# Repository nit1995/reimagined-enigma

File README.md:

# reimagined-enigma
India-H20 Project

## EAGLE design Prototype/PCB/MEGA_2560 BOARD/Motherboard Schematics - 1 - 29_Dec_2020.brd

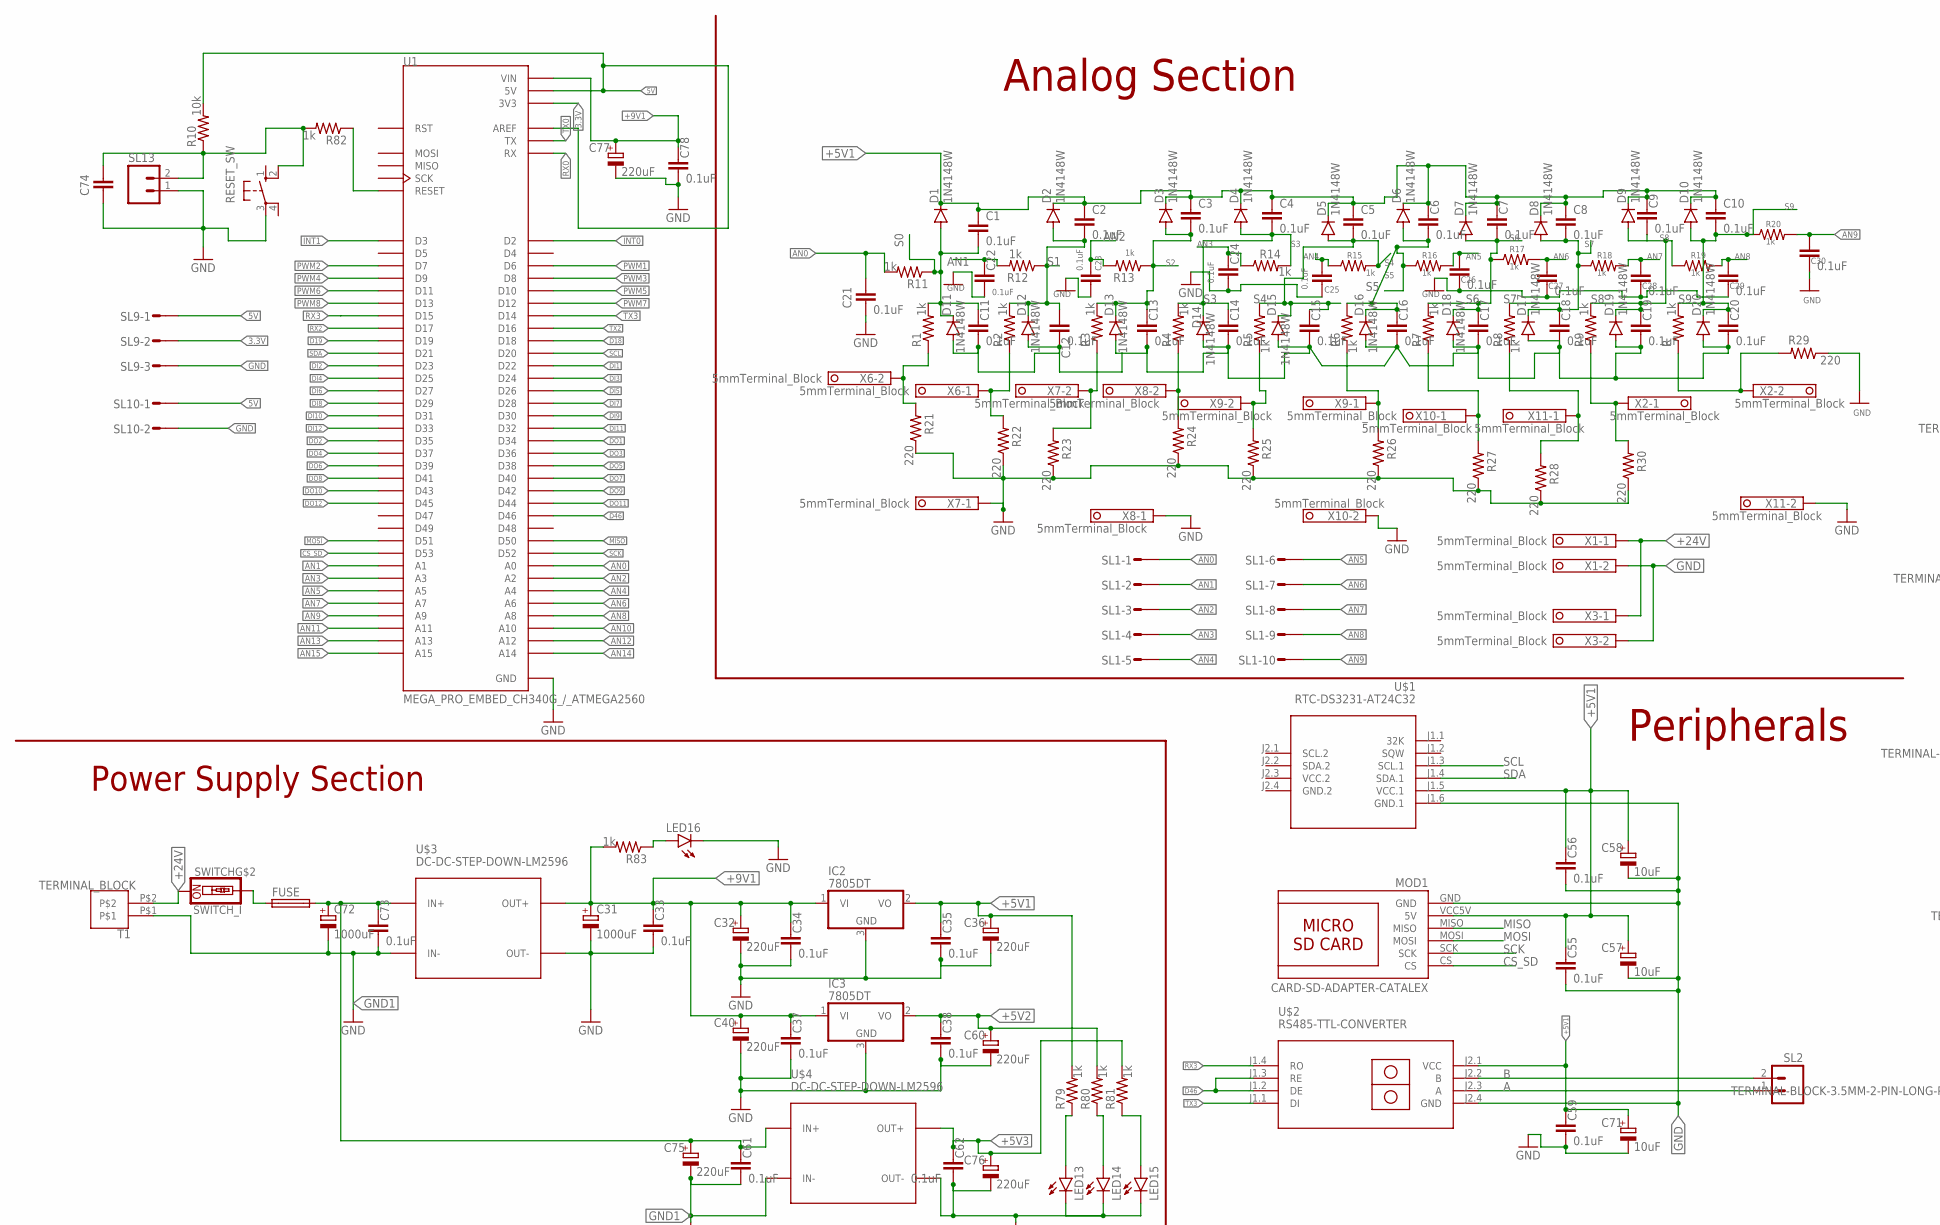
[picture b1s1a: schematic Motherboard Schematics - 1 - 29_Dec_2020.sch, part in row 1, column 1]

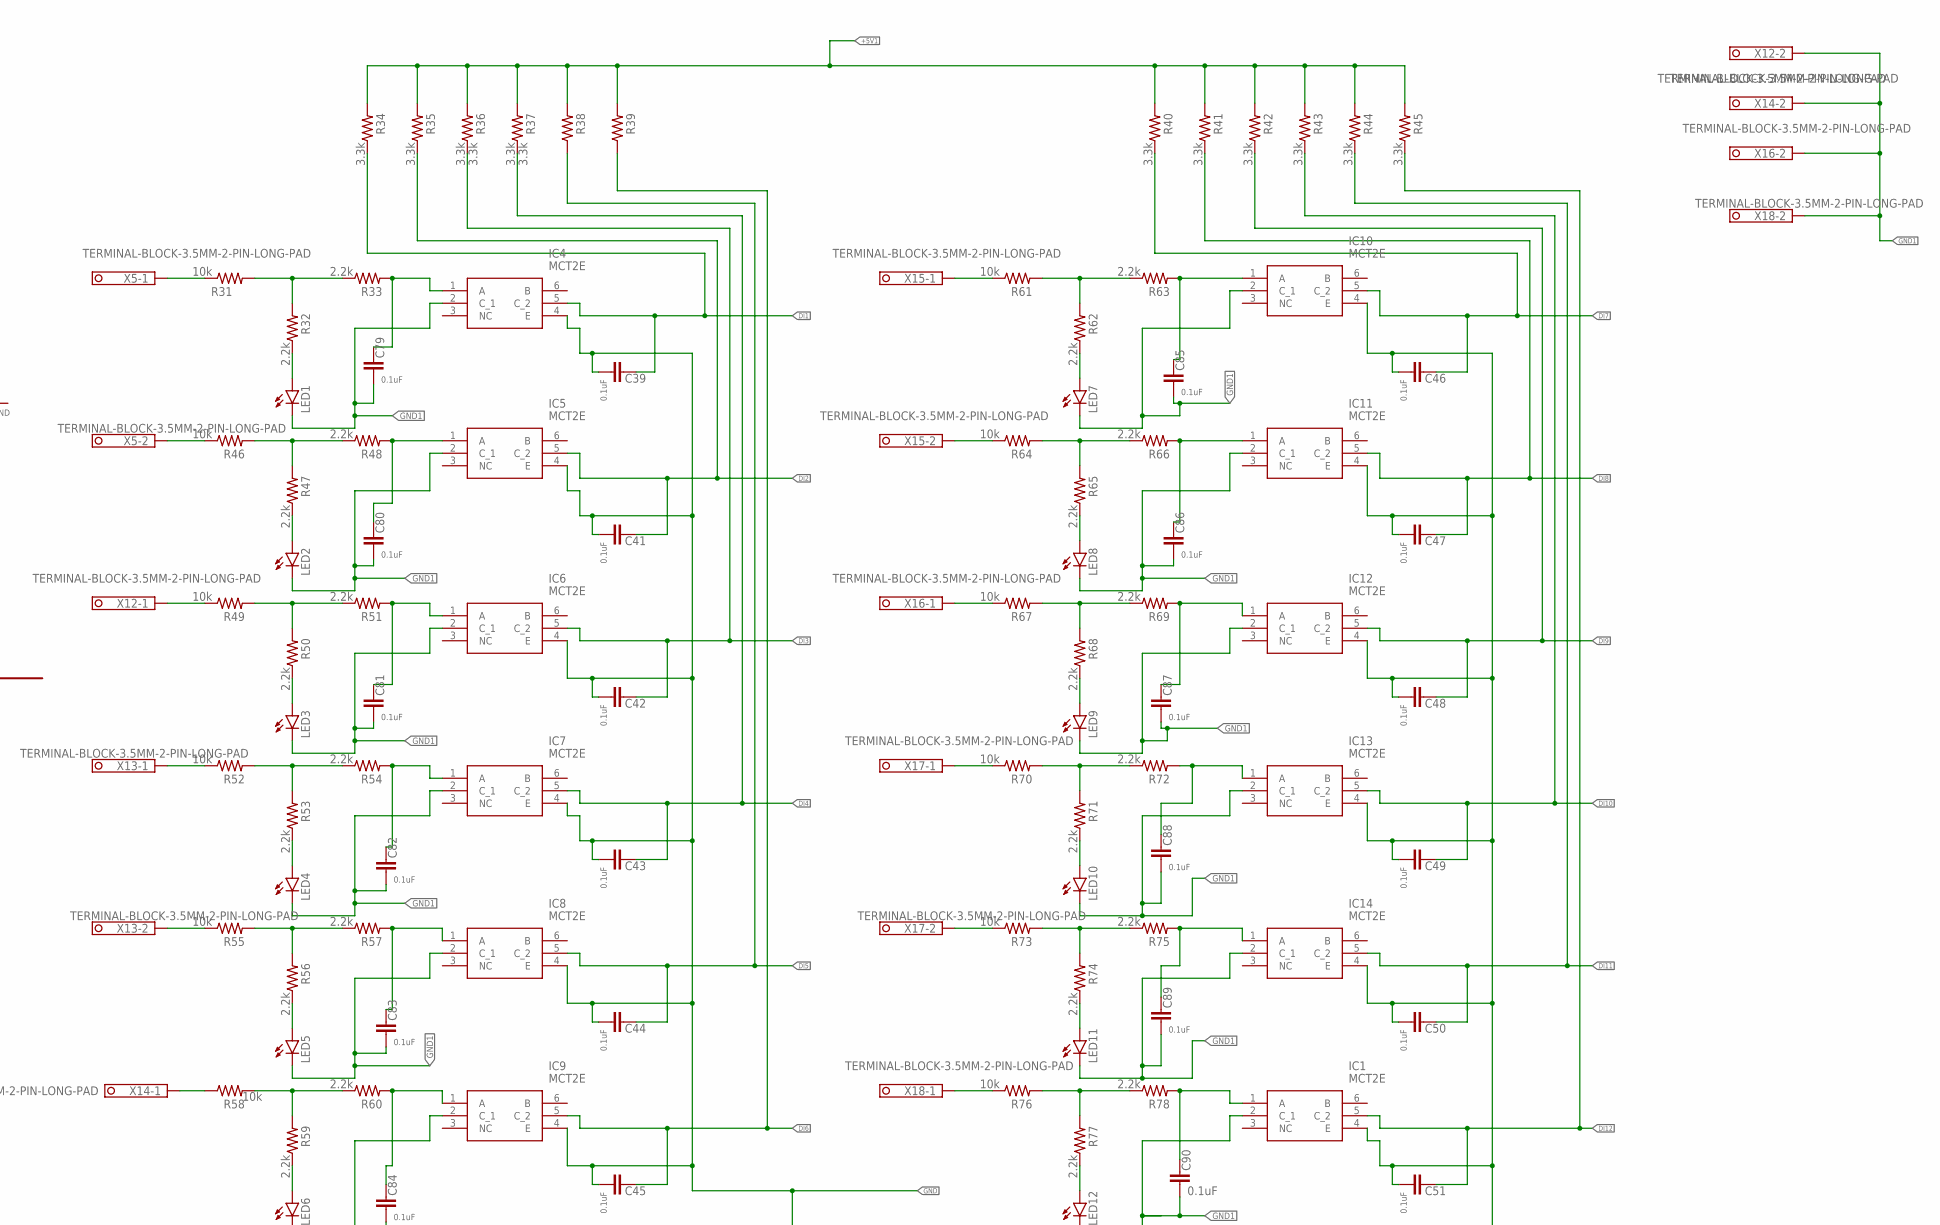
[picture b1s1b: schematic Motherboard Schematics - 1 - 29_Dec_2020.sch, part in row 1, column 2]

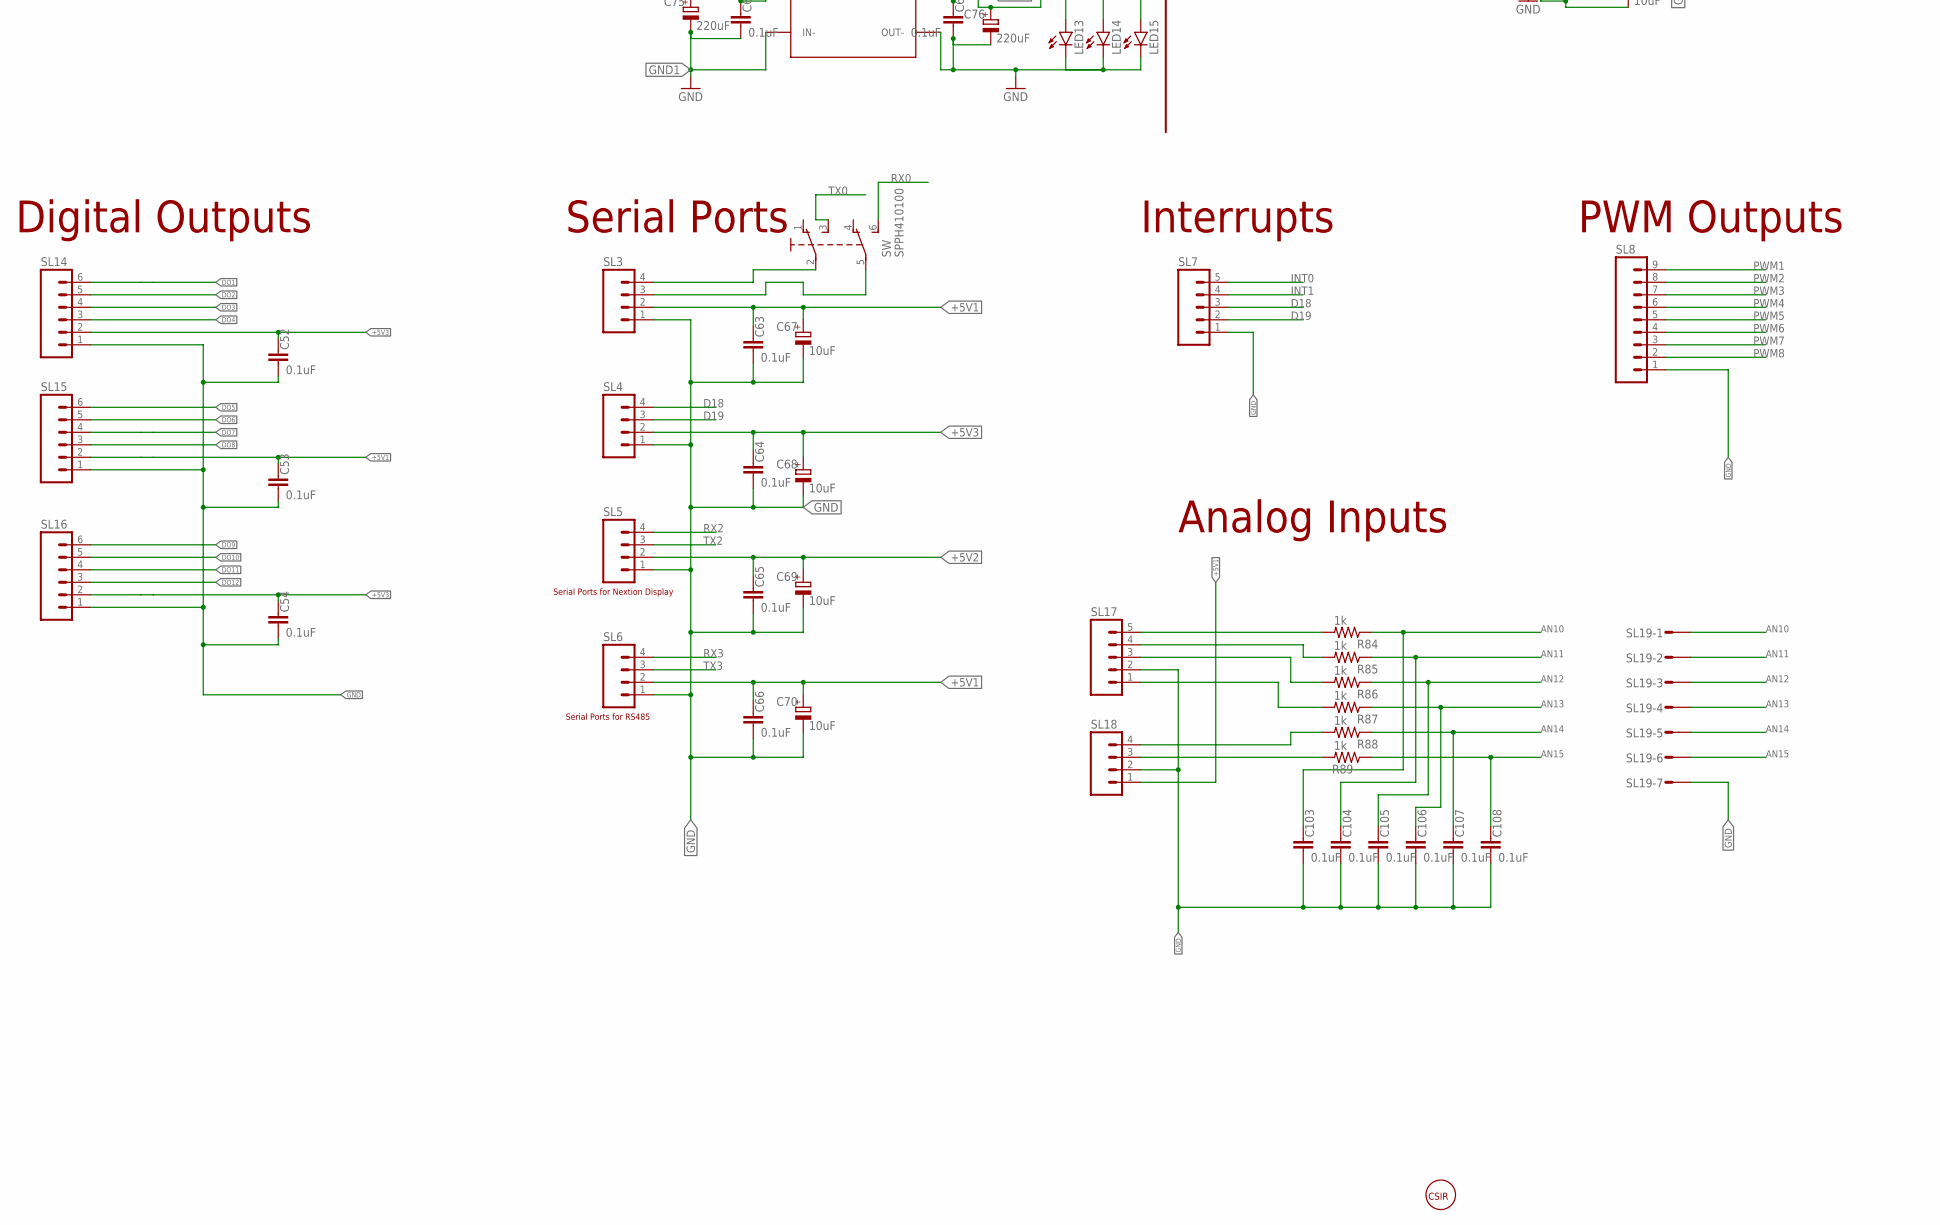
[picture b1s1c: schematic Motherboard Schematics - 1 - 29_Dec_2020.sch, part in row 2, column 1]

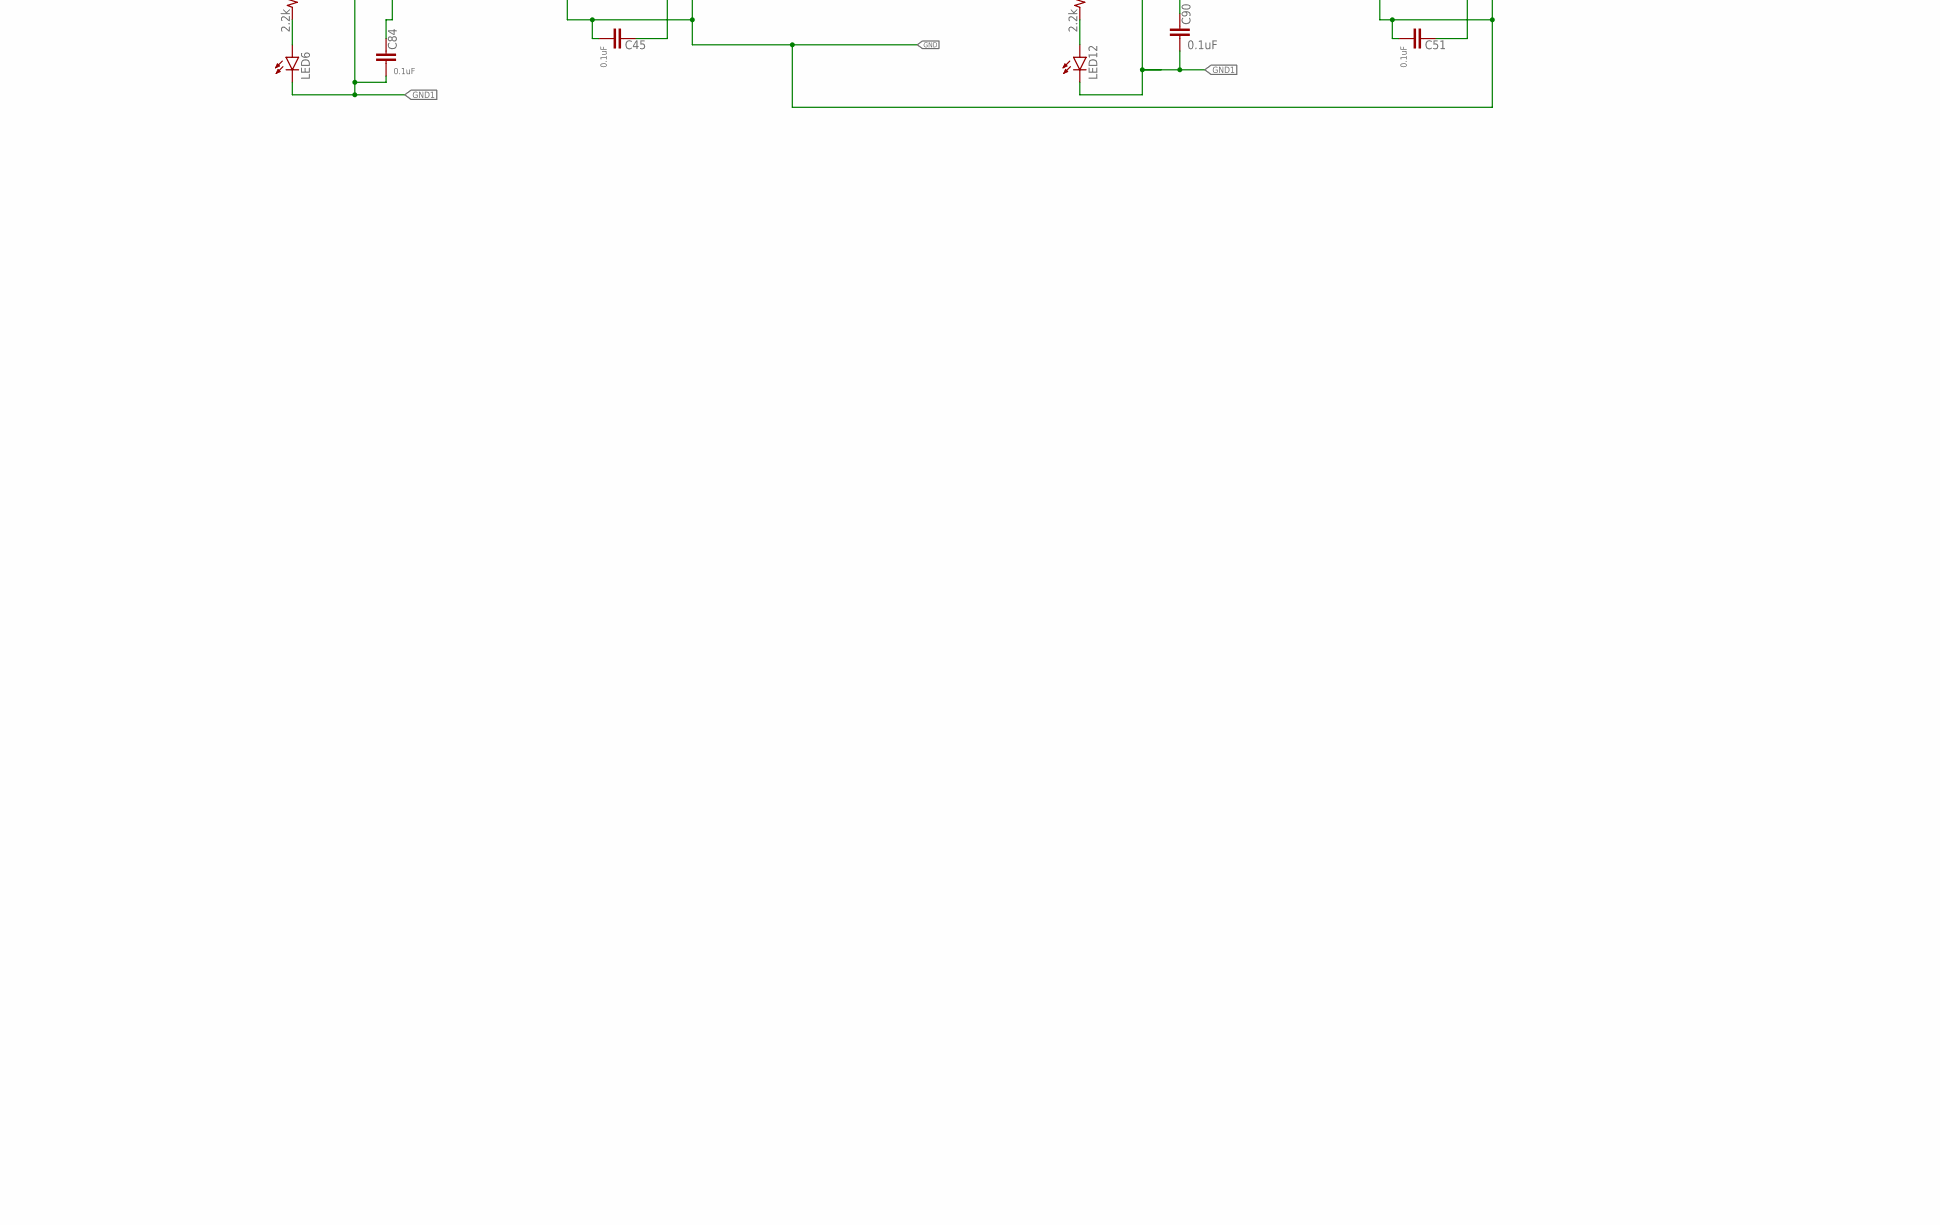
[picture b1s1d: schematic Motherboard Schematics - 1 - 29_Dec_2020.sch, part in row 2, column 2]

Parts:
C1, C2, C3, C4, C5, C6, C7, C8, C9, C10, C11, C12, C13, C14, C15, C16, C17, C18, C19, C20, C21, C22, C23, C24, C25, C26, C27, C28, C29, C30, C33, C34, C35, C37, C38, C39, C41, C42, C43, C44, C45, C46, C47, C48, C49, C50, C51, C52, C53, C54, C55, C56, C59, C61, C62, C63, C64, C65, C66, C73, C74, C78, C79, C80, C81, C82, C83, C84, C85, C86, C87, C88, C89, C90, C103, C104, C105, C106, C107, C108: 0.1uF; C1206
C31, C72: 1000uF; E7,5-16
C32, C36, C40, C60, C75, C76, C77: 220uF; E5-10,5
C57, C58, C67, C68, C69, C70, C71: 10uF; E2,5-7
D1, D2, D3, D4, D5, D6, D7, D8, D9, D10, D11, D12, D13, D14., D15, D16, D17, D18, D19, D20: 1N4148W; DO214AC
FUSE: SH22,5A
IC1, IC4, IC5, IC6, IC7, IC8, IC9, IC10, IC11, IC12, IC13, IC14: MCT2E; DIP762W60P254L712H480Q6N
IC2, IC3: 7805DT; TO252
LED1, LED2, LED3, LED4, LED5, LED6, LED7, LED8, LED9, LED10, LED11, LED12, LED13, LED14, LED15, LED16: LEDCHIPLED_1206; CHIPLED_1206
MOD1: CARD-SD-ADAPTER-CATALEX
R, R1, R2, R3, R4, R5, R6, R7, R8, R9, R11, R12, R13, R14, R15, R16, R17, R18, R19, R20, R79, R80, R81, R82, R83, R84, R85, R86, R87, R88, R89: 1k; R1206
R10, R31, R46, R49, R52, R55, R58, R61, R64, R67, R70, R73, R76: 10k; R1206
R21, R22, R23, R24, R25, R26, R27, R28, R29, R30: 220; R1206
R32, R33, R47, R48, R50, R51, R53, R54, R56, R57, R59, R60, R62, R63, R65, R66, R68, R69, R71, R72, R74, R75, R77, R78: 2.2k; R1206
R34, R35, R36, R37, R38, R39, R40, R41, R42, R43, R44, R45: 3.3k; R1206
RESET_SW: 10-XX; B3F-10XX
SL1: M10S; 10P
SL2, SL13: M02; 02P
SL3, SL4, SL5, SL6, SL18: M04; 04P
SL7, SL17: M05; 05P
SL8: M09; 09P
SL9: M03S; 03P
SL10: M02S; 02P
SL14, SL15, SL16: M06; 06P
SL19: M07S; 07P
SW: SPPH410100
SWITCH: SWITCH_I
T1: TERMINAL_BLOCK; BOC_TERMINAL
U1: MEGA_PRO_EMBED_CH340G_/_ATMEGA2560; MODULE_MEGA_PRO_EMBED_CH340G_/_ATMEGA2560
U$1: RTC-DS3231-AT24C32
U$2: RS485-TTL-CONVERTER
U$3, U$4: DC-DC-STEP-DOWN-LM2596
U$5: CSIR_LOGO
X1, X2, X3, X6, X7, X8, X9, X10, X11: 5mmTerminal_Block; TERMINAL-BLOCK-2-PIN-3.5MM-LONG-PAD
X5, X12, X13, X14, X15, X16, X17, X18: TERMINAL-BLOCK-3.5MM-2-PIN-LONG-PAD; TERMINAL-BLOCK-2-PIN-3.5MM-LONG-PAD

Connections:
3.3V: SL9.2, U1.3V3_1 (3V3), U1.3V3_2 (3V3)
5V: R10.2, SL9.1, SL10.1, U1.5V_1 (5V), U1.5V_2 (5V), U1.5V_3 (5V), U1.AREF
+5V1: C1.1, C2.1, C3.1, C4.1, C5.1, C6.1, C7.1, C8.1, C9.1, C10.1, C35.1, C36.+, C53.1, C55.1, C56.1, C57.+, C58.+, C59.1, C63.1, C66.1, C67.+, C70.+, C71.+, D1.C, D2.C, D3.C, D4.C, D5.C, D6.C, D7.C, D8.C, D9.C, D10.C, IC2.2 (VO), MOD1.VCC5V (5V), R34.2, R35.2, R36.2, R37.2, R38.2, R39.2, R40.2, R41.2, R42.2, R43.2, R44.2, R45.2, R79.2, SL3.2, SL6.2, SL15.2, SL18.1, U$1.J1.5 (VCC.1), U$2.J2.1 (VCC)
+5V2: C38.1, C60.+, C65.1, C69.+, IC3.2 (VO), R80.2, SL5.2
+5V3: C52.1, C54.1, C62.1, C64.1, C68.+, C76.+, R81.2, SL4.2, SL14.2, SL16.2, U$4.OUT+
+9V1: C31.+, C32.+, C33.1, C34.1, C37.1, C40.+, C77.+, C78.1, IC2.1 (VI), IC3.1 (VI), R83.2, U1.VIN_1 (VIN), U1.VIN_2 (VIN), U$3.OUT+
+24V: SWITCH.P$3, T1.P$2, X1.1, X3.1
A: SL2.1, U$2.J2.3 (A)
AN0: C21.1, R11.2, SL1.1, U1.A0
AN1: C22.1, R12.2, SL1.2, U1.A1
AN2: C23.1, R13.2, SL1.3, U1.A2
AN3: C24.1, R14.1, SL1.4, U1.A3
AN4: C25.1, R15.1, SL1.5, U1.A4
AN5: C26.1, R16.2, SL1.6, U1.A5
AN6: C27.1, R17.2, SL1.7, U1.A6
AN7: C28.1, R18.2, SL1.8, U1.A7
AN8: C29.1, R19.2, SL1.9, U1.A8
AN9: C30.1, R20.2, SL1.10, U1.A9
AN10: C103.1, R84.1, SL19.1, U1.A10
AN11: C104.1, R85.1, SL19.2, U1.A11
AN12: C105.1, R86.1, SL19.3, U1.A12
AN13: C106.1, R87.1, SL19.4, U1.A13
AN14: C107.1, R88.1, SL19.5, U1.A14
AN15: C108.1, R89.1, SL19.6, U1.A15
B: SL2.2, U$2.J2.2 (B)
CS_SD: MOD1.CS, U1.D53
D18: SL4.4, SL7.3, U1.D18
D19: SL4.3, SL7.2, U1.D19
D46: U1.D46, U$2.J1.2 (DE), U$2.J1.3 (RE)
DI1: C39.1, IC4.5 (C_2), R34.1, U1.D22
DI2: C41.1, IC5.5 (C_2), R35.1, U1.D23
DI3: C42.1, IC6.5 (C_2), R36.1, U1.D24
DI4: C43.1, IC7.5 (C_2), R37.1, U1.D25
DI5: C44.1, IC8.5 (C_2), R38.1, U1.D26
DI6: C45.1, IC9.5 (C_2), R39.1, U1.D27
DI7: C46.1, IC10.5 (C_2), R40.1, U1.D28
DI8: C47.1, IC11.5 (C_2), R41.1, U1.D29
DI9: C48.1, IC12.5 (C_2), R42.1, U1.D30
DI10: C49.1, IC13.5 (C_2), R43.1, U1.D31
DI11: C50.1, IC14.5 (C_2), R44.1, U1.D32
DI12: C51.1, IC1.5 (C_2), R45.1, U1.D33
DO1: SL14.6, U1.D34
DO2: SL14.5, U1.D35
DO3: SL14.4, U1.D36
DO4: SL14.3, U1.D37
DO5: SL15.6, U1.D38
DO6: SL15.5, U1.D39
DO7: SL15.4, U1.D40
DO8: SL15.3, U1.D41
DO9: SL16.6, U1.D42
DO10: SL16.5, U1.D43
DO11: SL16.4, U1.D44
DO12: SL16.3, U1.D45
GND: C21.2, C22.2, C23.2, C24.2, C25.2, C26.2, C27.2, C28.2, C29.2, C30.2, C31.-, C32.-, C33.2, C34.2, C35.2, C36.-, C37.2, C38.2, C39.2, C40.-, C41.2, C42.2, C43.2, C44.2, C45.2, C46.2, C47.2, C48.2, C49.2, C50.2, C51.2, C52.2, C53.2, C54.2, C55.2, C56.2, C57.-, C58.-, C59.2, C60.-, C62.2, C63.2, C64.2, C65.2, C66.2, C67.-, C68.-, C69.-, C70.-, C71.-, C74.2, C76.-, C77.-, C78.2, C103.2, C104.2, C105.2, C106.2, C107.2, C108.2, IC1.4 (E), IC2.3 (GND), IC3.3 (GND), IC4.4 (E), IC5.4 (E), IC6.4 (E), IC7.4 (E), IC8.4 (E), IC9.4 (E), IC10.4 (E), IC11.4 (E), IC12.4 (E), IC13.4 (E), IC14.4 (E), LED13.C, LED14.C, LED15.C, LED16.C, MOD1.GND, R21.1, R22.1, R23.1, R24.1, R25.1, R26.1, R27.1, R28.1, R29.1, R30.1, RESET_SW.3, SL3.1, SL4.1, SL5.1, SL6.1, SL7.1, SL8.1, SL9.3, SL10.2, SL13.1, SL14.1, SL15.1, SL16.1, SL17.2, SL18.2, SL19.7, U1.GND_1 (GND), U1.GND_2 (GND), U1.GND_3 (GND), U$1.J1.6 (GND.1), U$2.J2.4 (GND), U$3.OUT-, U$4.OUT-, X1.2, X3.2, X7.1, X8.1, X10.2, X11.2
GND1: C61.2, C72.-, C73.2, C75.-, C79.2, C80.2, C81.2, C82.2, C83.2, C84.2, C85.2, C86.2, C87.2, C88.2, C89.2, C90.2, IC1.2 (C_1), IC4.2 (C_1), IC5.2 (C_1), IC6.2 (C_1), IC7.2 (C_1), IC8.2 (C_1), IC9.2 (C_1), IC10.2 (C_1), IC11.2 (C_1), IC12.2 (C_1), IC13.2 (C_1), IC14.2 (C_1), LED1.C, LED2.C, LED3.C, LED4.C, LED5.C, LED6.C, LED7.C, LED8.C, LED9.C, LED10.C, LED11.C, LED12.C, T1.P$1, U$3.IN-, U$4.IN-, X12.2, X14.2, X16.2, X18.2
GND.2: U$1.J2.4 (GND.2)
INT0: SL7.5, U1.D2
INT1: SL7.4, U1.D3
MISO: MOD1.MISO, U1.D50
MOSI: MOD1.MOSI, U1.D51
unnamed: C11.2, C12.2, C13.2, C14.2, C15.2, C16.2, C17.2, C18.2, C19.2, C20.2, D11.A, D12.A, D13.A, D14..A, D15.A, D16.A, D17.A, D18.A, D19.A, D20.A
unnamed: R2.1, R22.2, X6.1
unnamed: R3.1, R23.2, X7.2
unnamed: R4.1, R24.2, X8.2
unnamed: R52.1, X13.1
unnamed: R58.1, X14.1
unnamed: R5.1, R25.2, X9.2
unnamed: R6.1, R26.2, X9.1
unnamed: R7.1, R27.2, X10.1
unnamed: R8.1, R28.2, X11.1
unnamed: R9.1, R30.2, X2.1
unnamed: R1.1, R21.2, X6.2
unnamed: FUSE.1, SWITCH.P$1
unnamed: R82.1, U1.RESET
unnamed: R.1, R29.2, X2.2
unnamed: R31.1, X5.1
unnamed: R31.2, R32.2, R33.1
unnamed: C79.1, IC4.1 (A), R33.2
unnamed: LED1.A, R32.1
unnamed: R55.1, X13.2
unnamed: R46.1, X5.2
unnamed: C88.1, IC13.1 (A), R72.2
unnamed: R46.2, R47.2, R48.1
unnamed: C80.1, IC5.1 (A), R48.2
unnamed: LED2.A, R47.1
unnamed: R73.1, X17.2
unnamed: R70.1, X17.1
unnamed: R49.1, X12.1
unnamed: R49.2, R50.2, R51.1
unnamed: C81.1, IC6.1 (A), R51.2
unnamed: LED3.A, R50.1
unnamed: R61.1, X15.1
unnamed: R61.2, R62.2, R63.1
unnamed: R64.1, X15.2
unnamed: R52.2, R53.2, R54.1
unnamed: C82.1, IC7.1 (A), R54.2
unnamed: LED4.A, R53.1
unnamed: C85.1, IC10.1 (A), R63.2
unnamed: R84.2, SL17.5
unnamed: SL3.4, SW.2
unnamed: C61.1, C72.+, C73.1, C75.+, FUSE.2, U$3.IN+, U$4.IN+
unnamed: C74.1, R10.1, R82.2, RESET_SW.2 (S1), SL13.2
unnamed: R55.2, R56.2, R57.1
unnamed: C83.1, IC8.1 (A), R57.2
unnamed: LED5.A, R56.1
unnamed: LED7.A, R62.1
unnamed: R58.2, R59.2, R60.1
unnamed: C84.1, IC9.1 (A), R60.2
unnamed: LED6.A, R59.1
unnamed: R85.2, SL17.4
unnamed: R64.2, R65.2, R66.1
unnamed: C86.1, IC11.1 (A), R66.2
unnamed: LED8.A, R65.1
unnamed: R67.1, X16.1
unnamed: R67.2, R68.2, R69.1
unnamed: C87.1, IC12.1 (A), R69.2
unnamed: LED9.A, R68.1
unnamed: R70.2, R71.2, R72.1
unnamed: LED13.A, R79.1
unnamed: LED10.A, R71.1
unnamed: LED14.A, R80.1
unnamed: R73.2, R74.2, R75.1
unnamed: C89.1, IC14.1 (A), R75.2
unnamed: LED11.A, R74.1
unnamed: R76.2, R77.2, R78.1
unnamed: C90.1, IC1.1 (A), R78.2
unnamed: LED12.A, R77.1
unnamed: R76.1, X18.1
unnamed: LED15.A, R81.1
unnamed: SL3.3, SW.5 (P1)
unnamed: R86.2, SL17.3
unnamed: LED16.A, R83.1
unnamed: R87.2, SL17.1
unnamed: R88.2, SL18.4
unnamed: R89.2, SL18.3
PWM1: SL8.9, U1.D6
PWM2: SL8.8, U1.D7
PWM3: SL8.7, U1.D8
PWM4: SL8.6, U1.D9
PWM5: SL8.5, U1.D10
PWM6: SL8.4, U1.D11
PWM7: SL8.3, U1.D12
PWM8: SL8.2, U1.D13
RX0: SW.6 (S1), U1.RX
RX2: SL5.4, U1.D17
RX3: SL6.4, U1.D15, U$2.J1.4 (RO)
S0: C1.2, C11.1, D1.A, D11.C, R1.2, R11.1
S1: C2.2, C12.1, D2.A, D12.C, R2.2, R12.1
S2: C3.2, C13.1, D3.A, D13.C, R3.2, R13.1
S3: C4.2, C14.1, D4.A, D14..C, R4.2, R14.2
S4: C5.2, C15.1, D5.A, D15.C, R5.2, R15.2
S5: C6.2, C16.1, D6.A, D16.C, R6.2, R16.1
S6: C7.2, C17.1, D7.A, D18.C, R7.2, R17.1
S7: C8.2, C18.1, D8.A, D17.C, R8.2, R18.1
S8: C9.2, C19.1, D9.A, D19.C, R9.2, R19.1
S9: C10.2, C20.1, D10.A, D20.C, R.2, R20.1
SCK: MOD1.SCK, U1.D52
SCL: U1.D20, U$1.J1.3 (SCL.1)
SDA: U1.D21, U$1.J1.4 (SDA.1)
TX0: SW.3 (S), U1.TX
TX2: SL5.3, U1.D16
TX3: SL6.3, U1.D14, U$2.J1.1 (DI)
VCC.2: U$1.J2.3 (VCC.2)

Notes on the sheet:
Analog Section
Power Supply Section
Digital Outputs
Peripherals
Serial Ports
Interrupts
PWM Outputs
Serial Ports for Nextion Display
Serial Ports for RS485
Analog Inputs

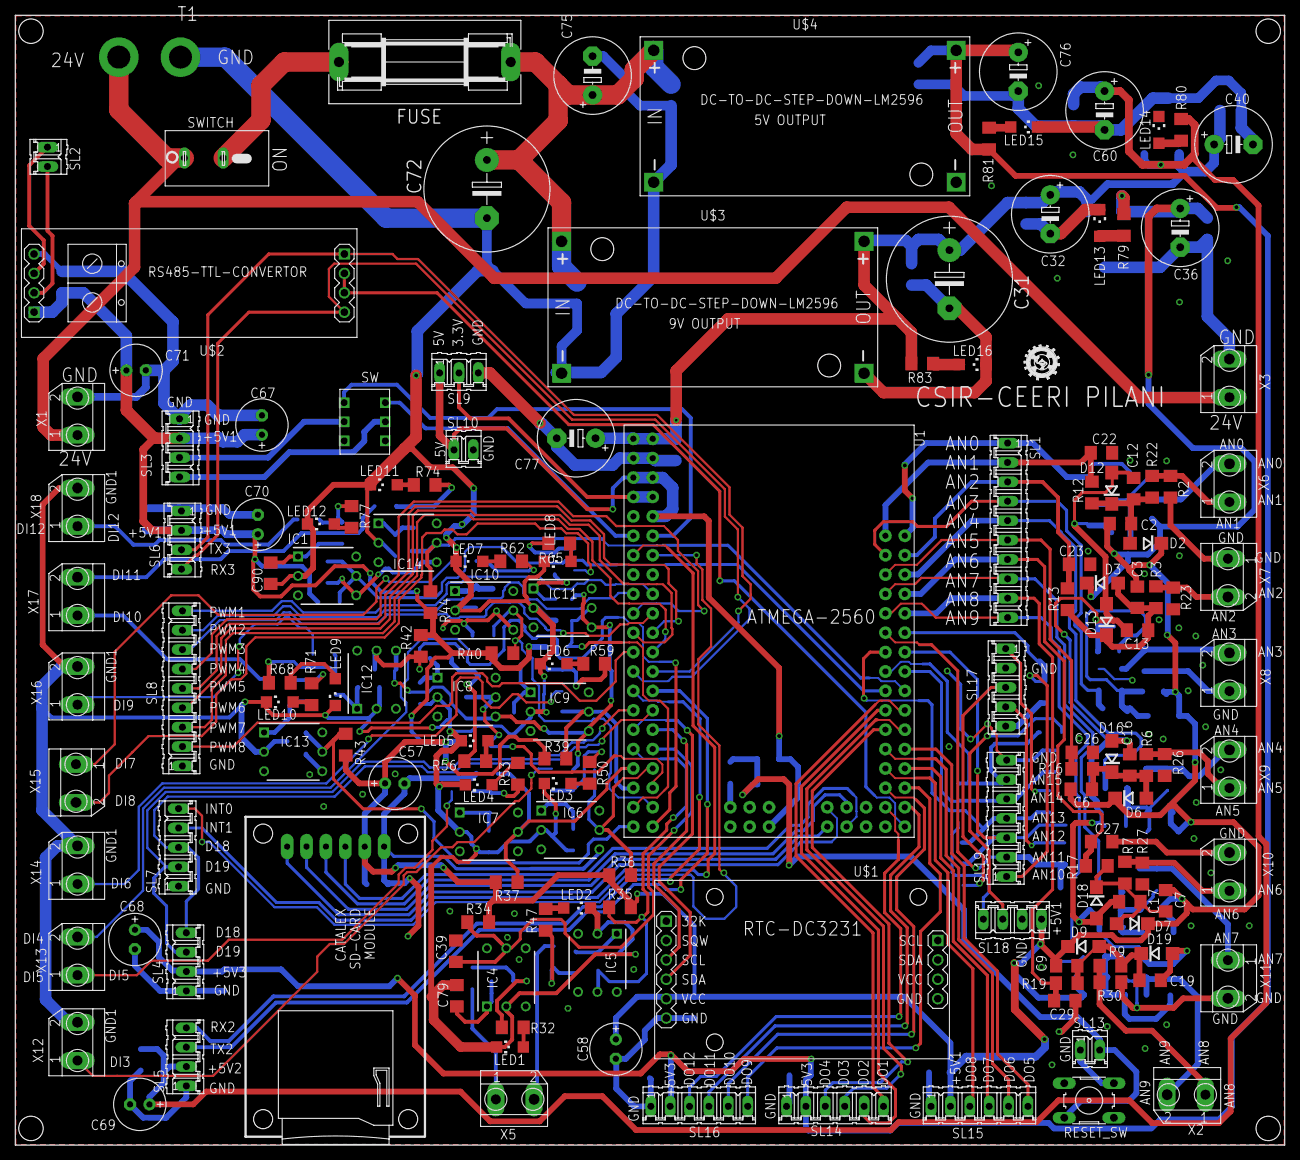
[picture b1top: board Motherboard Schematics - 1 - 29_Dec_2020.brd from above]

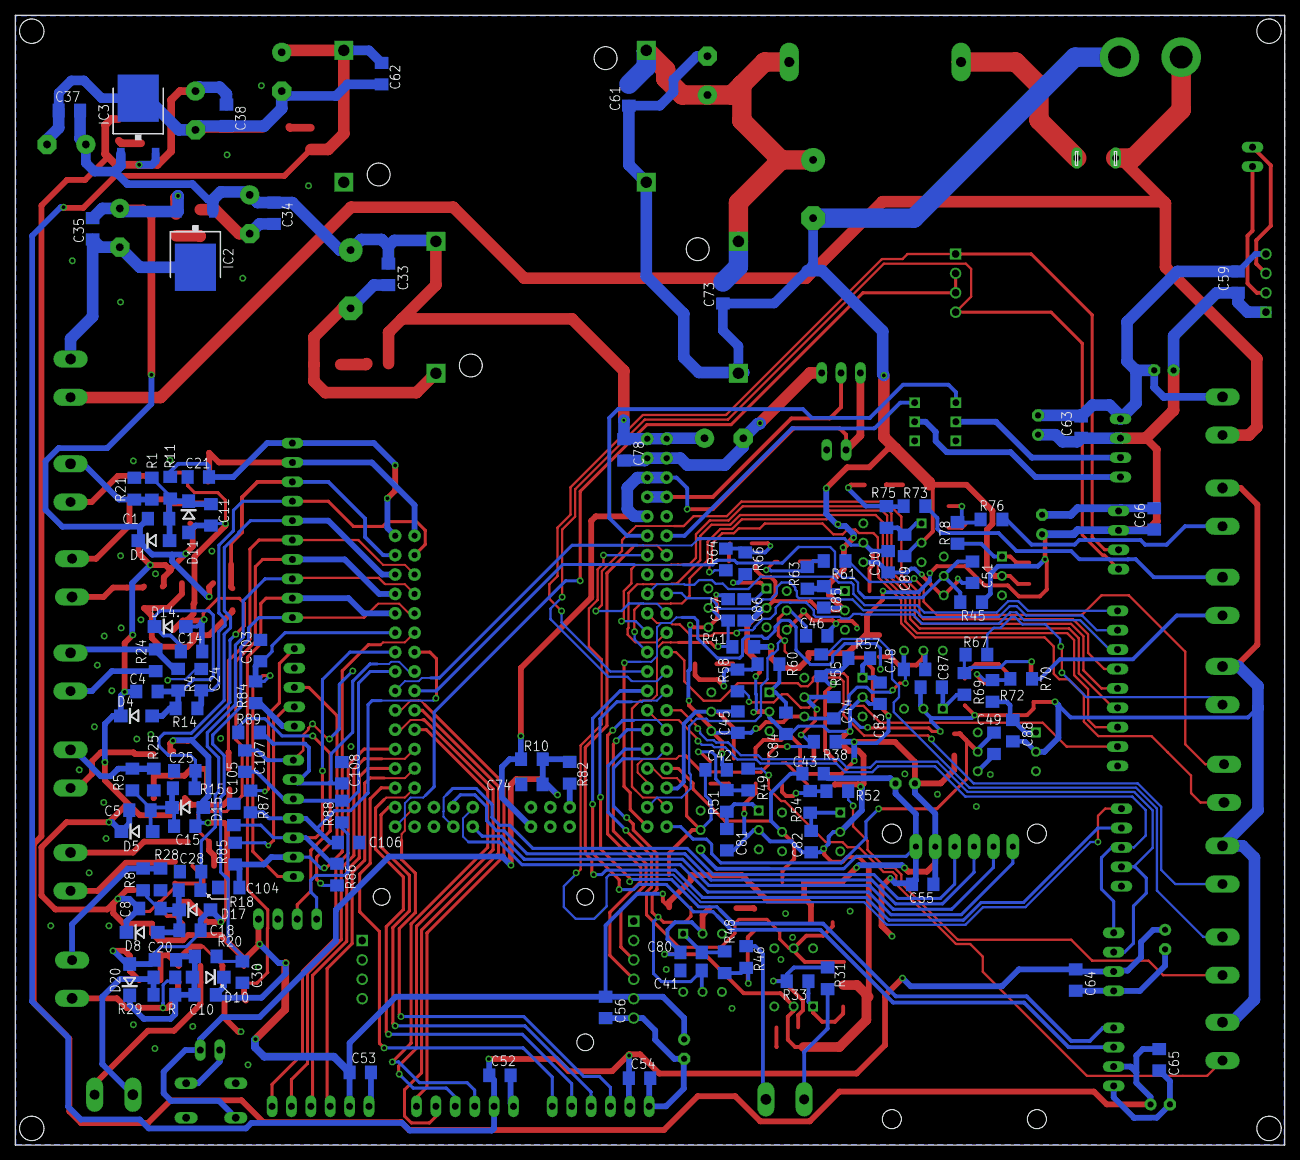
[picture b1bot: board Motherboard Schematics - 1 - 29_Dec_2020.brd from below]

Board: 2 copper layers, 166.3 x 148.0 mm, 282 parts (124 on the bottom side), 161 nets.

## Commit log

2021-03-13 Integrate DS3231 RTC
2021-03-13 Rename Errors in M1.txt to Errors in M1.md
2021-03-15 Create M2.ino
    Interface SD Card with EMCS to read and write files for datalogging.
2021-03-15 Create M3.ino
    Addition of pH Meter, Conductivity Meter and Level Sensors to M2.
2021-03-15 Add Sensors to M2
    Integrate pH Meter, Conductivity Meter and Level Sensor
2021-03-15 Integrate SD Card Memory to M1
2021-03-16 Create i2cscanner.ino
    To find the I2C address of devices connected.
2021-03-16 Integrate NEXTION display to M3
2021-03-16 Schematics for EMCS
2021-03-19 Update Log.md
    Added sleep and auto wake up on touch to Nextion display.
2021-03-19 Nextion GUI
2021-03-31 Added relay operation to level switch
2021-06-29 Add float sensors
    Program to read all 10 Magnetic Float Sensors to be installed in Lodhva and store the data in an SD Card with the timestamp. Added all 10 float sensors from LAH-001 to LAH-006 and LAL-001 to LAL-005
2021-06-30 Update M5.ino
    write_SD() function to add datastring to SD Card. Tank level status variables made as global variables
2021-06-30 Create M6.ino
    Code to implement Conductivity Sensors in EMCS and write in SD Card
2021-07-26 Create M7.ino
    Program to read pH meter
2021-07-26 Create M5.ino
    Fixed the return level issue
2021-07-27 Update M6.ino
    Correction of measure_conductivity() function by adding input of analog pins

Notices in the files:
parts and their libraries:
diy-modules: Released under the Creative Commons Attribution 4.0 International License: http://creativecommons.org/licenses/by/4.0
